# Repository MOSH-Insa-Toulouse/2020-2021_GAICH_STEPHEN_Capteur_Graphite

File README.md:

# 2020-2021 : Capteur Graphite GAICH-STEPHEN 
2020-2021 : Projet réalisé dans le cadre de l'Unité de Formation "du capteur au banc de test" en 4ème année Génie Physique, à l'INSA de Toulouse. Au cours de ce projet, nous avons réalisé un capteur de déformation/ jauge de contrainte à base de graphite 3H à 3B. Afin de mesurer la résistance de ce type de crayon, nous avons crée un dispositif bas-coût et transportable qui fut proposé par nos enseignants. Nous avons réalisé et fabriqué un PCB shield, à l'aide du logiciel Kicad, contenant un amplificateur transimpédance (circuit analogique) , un module Bluetooth, un écran OLED et un encodeur rotatoire. Ce dernier est pluggé sur un microcontrôleur Arduino Uno programmé à l'aide du logiciel Arduino IDE et contrôlé par une application android APK bluetooth. 

*** 
  - [Livrables](#livrables)
  - [PCB Shield](#pcb-shield)
  - [Code Arduino Mesure](#code-arduino-mesure)
  - [Application android APK](#application-android-apk)
  - [Banc de test](#banc-de-test)
  - [Code Arduino du banc de test](#code-arduino-du-banc-de-test)
  - [Protocole de test du capteur et les résultats obtenus](#protocole-de-test-du-capteur-et-les-résultats-obtenus)
  - [Datasheet capteur graphite](#datasheet-capteur-graphite)
  - [Problèmes rencontrés et améliorations à réaliser](#problèmes-rencontrés-et-améliorations-à-réaliser) 

*** 
## Livrables  

- [x] PCB shield 
- [x] Code Arduino permettant la mesure de R et le contrôle des fonctionnalités BT, OLED... 
- [x] Application android APK réalisé avec MIT APP INVENTOR.
- [x] Protocole de mesure et le programme Arduino pour le banc de test
- [x] Datasheet du capteur de déformation/ jauge de contrainte 

## PCB Shield
Utilisation des outils présents dans le logiciel Kicad pour créer le PCB: 
[KiCad EDA - Schematic Capture & PCB Design Software](https://kicad-pcb.org/), version: 5.1.8 

Le PCB Shield est pluggé sur un microcontrôleur Arduino Uno. Un amplificateur transimpédance, un module BT, un écran OLED et un encodeur rotatoire sont présents. 

Librairies de composants:
* Capacitor THT
* Resistor THT 
* Arduino Uno

#### Composants créés : symboles & empreintes 

- *Capteur Graphique*

- *Module Bluetooth*

- *Encodeur rotatoire Keyes KY 040*

- *Ecran OLED*

- *Amplificateur LT1050* (Empreinte déjà présente : DIP-8_W7.62mm_LongPads)

#### Schématique 

Dans le Eeschema, crée à partir d'un modèle Arduino Uno, nous avons regroupé les éléments suivant trois groupes : l'amplificateur transimpédance (circuit analogique qui permet de traiter les données envoyées par le capteur (variation de résistance)), les modules permettant d'ajouter des fonctionnalités au micro-contrôleur (module Bluetooth, encodeur rotatoire, écran OLED) et les broches de la carte Arduino Uno.  

#### Placement des composants 

#### Routage 3D

#### Soudage du PCB

Grâce à Catherine Crouzet, travaillant au Génie Physique, INSA Toulouse, nous avons pu réaliser notre PCB. Après avoir réalisé le schéma électrique, le placement des composants et le routage de la carte PCB sur le logiciel KiCad, le typon du PCB est imprimé sur deux feuilles calques. Les deux transparents sont alors superposés et scotchés entre eux afin de diminuer le risque de microcoupure (encre trop pale). Le typon est disposé sur la glace de l’insoleuse ainsi que la plaque d’époxy dont la face cuivrée (60µm) photosensible est "collée" au typon. Cette opération dure environ deux minutes et permet d’insoler la face photosensible. Le dessin du typon est alors visible sur la face cuivrée. La plaque est ensuite plongée dans un révélateur jusqu’à ce que le dessin apparaisse parfaitement (retire la résine non insolée). Après l’avoir rincé à l’eau, la plaque est alors prête pour la gravure. Le PCB est alors place dans un bain de perchlorure de fer rongeant tout le cuivre non protégé par la résine pendant sept minutes. Après l’avoir rincée à l’eau et vérifié le circuit, la résine est retirée avec de l’acétone. Le PCB sera ensuite percé et les composants seront soudés. 

Passons ensuite au perçage des trous de la plaquette à l'aide d'une perçeuse électrique [ici](Images/Perçeuse.jpg).
- 0.8mm pour ceux de l'AOP, des résistances et des capacités.
- 1mm pour ceux des connecteurs de l'Arduino et des headers des différents modules (pinces pour la feuille de graphite, bluetooth, encodeur rotatoire, écran OLED)

Pour finir, nous avons soudé chaque composant à l'aide d'un fer à souder. 

Remarque: il aurait fallu faire le diamètre des pads des connecteurs arduino plus gros afin d'avoir des soudures parfaites => peu de cuivre qui est resté autour après le perçage, ce qui a compliqué la soudure. 

#### Détail sur le conditionneur du capteur réalisé sur le shield (électronique analogique)
Nous avons détaillé cette partie dans la datasheet à la page 5 et 6 [ici](Datasheet/Datasheet_jauge_contrainte_GPINSA2021-2494-5215.pdf)

## Code Arduino Mesure 
Utilisation de l'environnement Arduino IDE téléchargeable [ici](https://www.arduino.cc/en/software); version 1.8.13.

Les librairies que nous avons utilisées sont disponibles [ici](PGM_Arduino_Mesure/Librairie).

Nous avons développé un programme permettant de mesurer la résistance de notre capteur. Vous pouvez le retrouver [ici](PGM_Arduino_Mesure/Programme_Capteur_Mesure/Programme_Capteur_Mesure.ino). 
Il s'agit d'un programme basique qui lira la valeur de la tension sur le pin A0 nommé comme "capteurgraphite". Cette acquisition est cadencée à 1s. La valeur lue est ensuite mappée sur 1 byte (0 à 255) car nous avons choisi d'envoyer un chiffre d'un byte sur le bluetooth. L'APK recevra un chiffre d'un byte à chaque tour de boucle. Cette valeur est également affichée sur le port série.

## Application android APK
Utilisation du site MIT App Inventor : [ici](https://appinventor.mit.edu/). 

Nous récupérons les données envoyées par le module bluetooth HC05 sur l'application et créons un fichier pour stocker ces dernières. 
Après de nombreux problèmes avec cet environnement et en s'inspirant du code crée par M.Grisolia, nous avons pu développer cette application. 

Face avant 

Une connexion avec le bluetooth HC05 est nécessaire. Puis, vous pourrez suivre la variation de la tension lue par l'APK "en direct". La valeur de la résistance du capteur est aussi calculée et affichée en bas de l'écran. Enfin, un fichier contenant toutes les données récupérées par le bluetooth est créé dans vos documents. 

Vous trouverez le fichier .aia [ici](APK_Bluetooth/CAPTEUR_GRAPHITE_FILE.aia) et le fichier .apk [ici](APK_Bluetooth/CAPTEUR_GRAPHITE_FILE.apk)

Nous avons essayé d'améliorer cette version en faisant plusieurs screens. 
Une page d'accueil présente ci-dessous : 

Ensuite, sur la deuxième page après avoir cliqué sur le bouton "commencer l'acquisition", vous devez réaliser la mesure de la résistance initiale du capteur. Lorsque tous les voyants de l'étape 1 se mettent au vert, vous pouvez voir le tracé de la variation de la tension Vadc en fonction du temps au cours du temps. Les valeurs de la résistance du capteur et de la résistance relative sont aussi affichées.

Vous trouverez le fichier .aia [ici](APK_Bluetooth/Application_Capteur_amelioree.aia) et le fichier .apk [ici](APK_Bluetooth/Application_Capteur_amelioree.apk)

Plusieurs améliorations peuvent être réalisées. Nous les détaillerons dans la partie "Problèmes rencontrés et améliorations à réaliser".

## Banc de test 
Nous avons réalisé deux bancs de test "low-tech". Nous avons détaillé sa construction dans la datasheet afin que toute personne possédant notre capteur puisse retrouver les résultats que nous avons obtenus [ici](Datasheet/Datasheet_jauge_contrainte_GPINSA2021-2494-5215.pdf) à la page 7-8. De plus, étant réalisé à base de déchets ménagers, aucun matériel de haute technologie n'est nécessaire. 

Nous vous présentons nos deux bancs de test : 

Figure : Banc de test « low-tech » n°1_ récupération de déchets divers

Figure : Banc de test « low-tech » n°2 _ carton

Au début, afin de diminuer les faux contacts entre les deux pinces crocodiles, nous avions utilisé un rouleau de papier toilette que nous avions troué (voir la photo ci-dessous).
Nous n'avons pas gardé cette méthode pour les mesures en tension et compression car les cercles créés sur le banc n'était pas à la même hauteur (amélioration possible).

## Code Arduino du banc de test 
Nous avons développé ce programme arduino afin de déterminer les valeurs obtenues en utilisant notre banc de test : [ici](PGM_Banc_de_test/PGM_Banc_de_test.ino).

Pour ce faire, nous avons du améliorer une librairie nous permettant de faire le "debouncing" sur l'encodeur rotatoire [ici](PGM_Arduino_Mesure/Librairie/Encoder_Polling_V2).

Notre nouveau programme gère aussi l'encodeur rotatoire et l'écran OLED. Ayant plusieurs banc de tests, nous avons programmé un menu sur l'écran OLED permettant à l'utilisateur de choisir le type de banc de test souhaité. Le boutton poussoir de l'encodeur rotatoire permet de selectionner ce dernier. Une fois le type de banc de test choisi, le programme envoie le type de banc de test à l'APK sous forme de "string" (texte). Dans le fichier des données enregistré sur le téléphone portable, chaque acquisition commence par des informations sur l'acquisition (banc de test, clock, forme des données reçues etc). Une fois cette étape terminée, l'OLED affiche la question "le bluetooth est- il connecté ?". L'utilisateur doit confirmer que la connexion a été établie en appuyant sur "Oui". Ensuite, il affiche "Etes-vous prêts ?" . L'utilisateur appuie de nouveau sur "Oui" une fois prêt. L'acquisition commence. La valeur de la tension Vadc est affichée sur l'OLED et est envoyée à l'APK via le bluetooth. Quand l'utilisateur souhaite arrêter l'acquistion, il doit appuyer sur le bouton 'STOP'. L'acquisition est alors arrêtée et l'OLED affiche de nouveau le menu principal.

## Protocole de test du capteur et les résultats obtenus 
Nous avons réalisé différentes expériences afin de déterminer les caractéristiques de notre capteur. 

#### Influence des dimensions du capteur 

Dans un premier temps, nous avons souhaité étudier l'influence des dimensions du capteur sur la résistance initiale. De ce fait, nous avons réalisé un plan d'expérience avec un modèle linéaire sans interactions de type TRI. Veuillez consulter ce document pour plus de détails sur la démarche : [ici](Banc_de_test&résultats/Banc_test_recherche_meilleur_capteur.docx) et sur les résultats obtenus [ici](Banc_de_test&résultats/Plan d'expérience_meilleures_dimensions.xlsx).

Nous avons pu identifier la réalité expérimentale (variables aléatoires de mesure) et tenter d’expliquer puis de maitriser au mieux les paramètres ayant un impact sur la résistance de notre capteur. Nous n’assurons pas que tous les paramètres influents furent identifiés. Elles ont aussi permis de vérifier que la résistance de notre capteur suivait la loi de Pouillet et donc la loi d’Ohm. Etant donné que nous ne sommes pas capables de déterminer le nombre de feuillets de graphite déposé lors du coloriage de notre capteur, nous allons étudier la variation relative en résistance ∆R/R_o = (R_mes-R_o)/R_o  afin d’homogénéiser nos mesures et pouvoir les comparer.  

#### Zone de non-déterioration du capteur

Dans un deuxième temps, nous nous avons essayé de determiner la zone de non-destruction du capteur. Après chaque mesure sur un rayon de courbure, nous avons noté la valeur de la tension du capteur au repos (non déformé) puis avons déterminé la résistance de ce dernier. Nous l’avons ensuite comparé à celle mesurée au début de la série de mesure. 
Document excel  [ici](Banc_de_test&résultats/Determination_zone_non_destruction_capteur.xlsx)

Figure : |Vadc_après_chaque_mesure - Vadc_initiale| après chaque déformation pour le capteur en tension

Figure : |Vadc_après_chaque_mesure - Vadc_initiale| après chaque déformation pour le capteur en compression

Voici notre conclusion : 

#### Influence du type de crayon utilisé pour colorier le capteur

Ensuite, nous avons étudie l'influence du type de crayon utilisé pour colorier notre capteur. Les crayons 3H, 2H, H, HB, B, 2B, et 3B furent testés successivement pour colorier notre capteur. Des tests de déformation, utilisant différents rayons de courbure de notre banc de test, sur ces capteurs furent réalisés. Ces informations sont présentes sur ces différents graphiques. Pour de détails, consultez le document excel [ici](Banc_de_test&résultats/Mesure_RayonCoubure_Crayons_Papiers.xlsx). 

Figure : Graphique représentant la variation relative de la résistance en fonction de la déformation en tension du capteur et du type de crayon présent sur le capteur

Figure : Graphique représentant la variation relative de la résistance en fonction de la déformation en compression du capteur et du type de crayon présent sur le capteur

En conclusion de cette étude, le capteur colorié avec un crayon 3H est le plus sensible. En effet, pour ce capteur, la variation relative de la résistance ΔR/Ro est la plus grande. Cependant, en effectuant plusieurs expériences (colorier différents capteurs avec ce crayon), nous observons une large variabilité de la réponse. Lorsque le capteur est colorié avec des crayons 2H, H, HB, B, 2B et 3B, un comportement linéaire du ce dernier est observé. La sensibilité se définit comme le rapport entre sa valeur de sortie et sa valeur d'entrée. Lorsque le capteur est soumis à un mouvement de tension et de compression, la sensibilité du capteur augmente avec la dureté du crayon utilisé. En l’occurrence, le capteur colorié avec le crayon 3H est le plus sensible et celui colorié avec le crayon 3B est le moins sensible.

#### Influence du type de papier du capteur 

Enfin, nous avons étudié l'influence de type de papier. Nous avions émis l'hypothèse que la réponse du capteur serait différente en fonction du type de papier utilisé. Quand le capteur est réalisé sur du papier normal (70g/m²), la valeur de la résistance est trop faible pour être mesurée par notre conditionneur. La valeur de la tension Vadc est en saturation (5V). Une corrélation entre l’épaisseur du papier utilisé et la réponse du capteur existe. Nous avons détaillé une possible explication à ce phénomène dans la datasheet à la page 15. [ici](Datasheet/Datasheet_jauge_contrainte_GPINSA2021-2494-5215.pdf)

Pour pallier ce problème, le papier fut renforcé en enveloppant le capteur avec du ruban d’adhésif sans couvrir les pads du capteur pour la prise du contact avec les pinces crocodiles. Vous trouverez les résultats obtenus dans le fichier excel [ici](Banc_de_test&résultats/Influence_scotch.xlsx). En effectuant plusieurs tests sur le capteur, une tendance d'augmentation de la résistance est observée lorsque nous diminuons le rayon de courbure. Cependant, nous pouvons observer une augmentation initiale de la résistance entre un capteur scotché et un capteur sans ruban adhésif. Nous n’avons pas observé une amélioration de la zone de non-destruction. Dans certains cas, nous observons même une dégradation de cette dernière. Nous avons détaillé une possible explication à ce phénomène dans la datasheet à la page 15. [ici](Datasheet/Datasheet_jauge_contrainte_GPINSA2021-2494-5215.pdf)

## Datasheet capteur graphite
Vous pouvez retrouver la datasheet complète de notre capteur [ici](Datasheet/Datasheet_jauge_contrainte_GPINSA2021-2494-5215.pdf)

## Problèmes rencontrés et améliorations à réaliser

#### Problèmes sur le PCB

- Pads pour les connecteurs arduino trop fins.
- Mauvais placement de l'empreinte OLED : En testant l'écran OLED avec un programme fourni dans les libraires arduino, nous nous sommes rendus compte que, par inattention, nous avions mal placé l'empreinte (rotation 180°) car nous souhaitions que l'écran OLED soit positionné vers l'extérieur (cf PCB 3D). Afin d'avoir les bonnes pins, ce dernier doit être placé à l'intérieur. Or il y a l'encodeur rotatoire. Pour palier à ce problème, nous allons utiliser la platine d'expérimentation ou des fils males/femelle. 

  Améliorations : Nouveau PCB. 

#### Amélioration de l'application APK : Application capteur améliorée 
Après de multiples essais, nous n'avons pas réussi à afficher correctement la variation (dR-Ro)/Ro. Nous ne comprenons pas l'erreur commise. 
De plus, il faudrait optimiser le code pour que le traçage sur le canvas et les calculs de résistance se fassent en "temps réel". Nous avons un temps de décalage assez important. 
  
#### Améliorations sur la caractérisation du capteur 

Veuillez vous référer à notre datasheet présente [ici](Datasheet/Datasheet_jauge_contrainte_GPINSA2021-2494-5215.pdf) section Suggestions/Remarques. 

Nous avons détaillé différentes expérimentations que nous aurions aimées mener. Par manque de temps, nous n'avons pu les faire. 
De plus, afin de determiner concrètement les dimentions optimales du capteur, le plan d'expérience que nous avons mené devrait être complété par une étude plus approfondie (modèle de 2nd ordre) pour determiner l'optimum. Cependant, il faut pouvoir maitriser des paramètres qui ne sont pas contrôlables pour le moment (nombre de feuillets de graphite sur le capteur). 

***

## Note des auteurs 
Nous tenons à remercier Mme Crouzet, M.Grisolia et M.Biganzoli pour leur aide tout au long de ce projet ainsi que M.Constancias pour son aide lors de l'analyse des résultats obtenus sur notre DOE. 

Pour nous contacter : 
- Eléonore Gaich : gaich@etud.insa-toulouse.fr
- Calvin Stephen : stephen@etud.insa-toulouse.fr

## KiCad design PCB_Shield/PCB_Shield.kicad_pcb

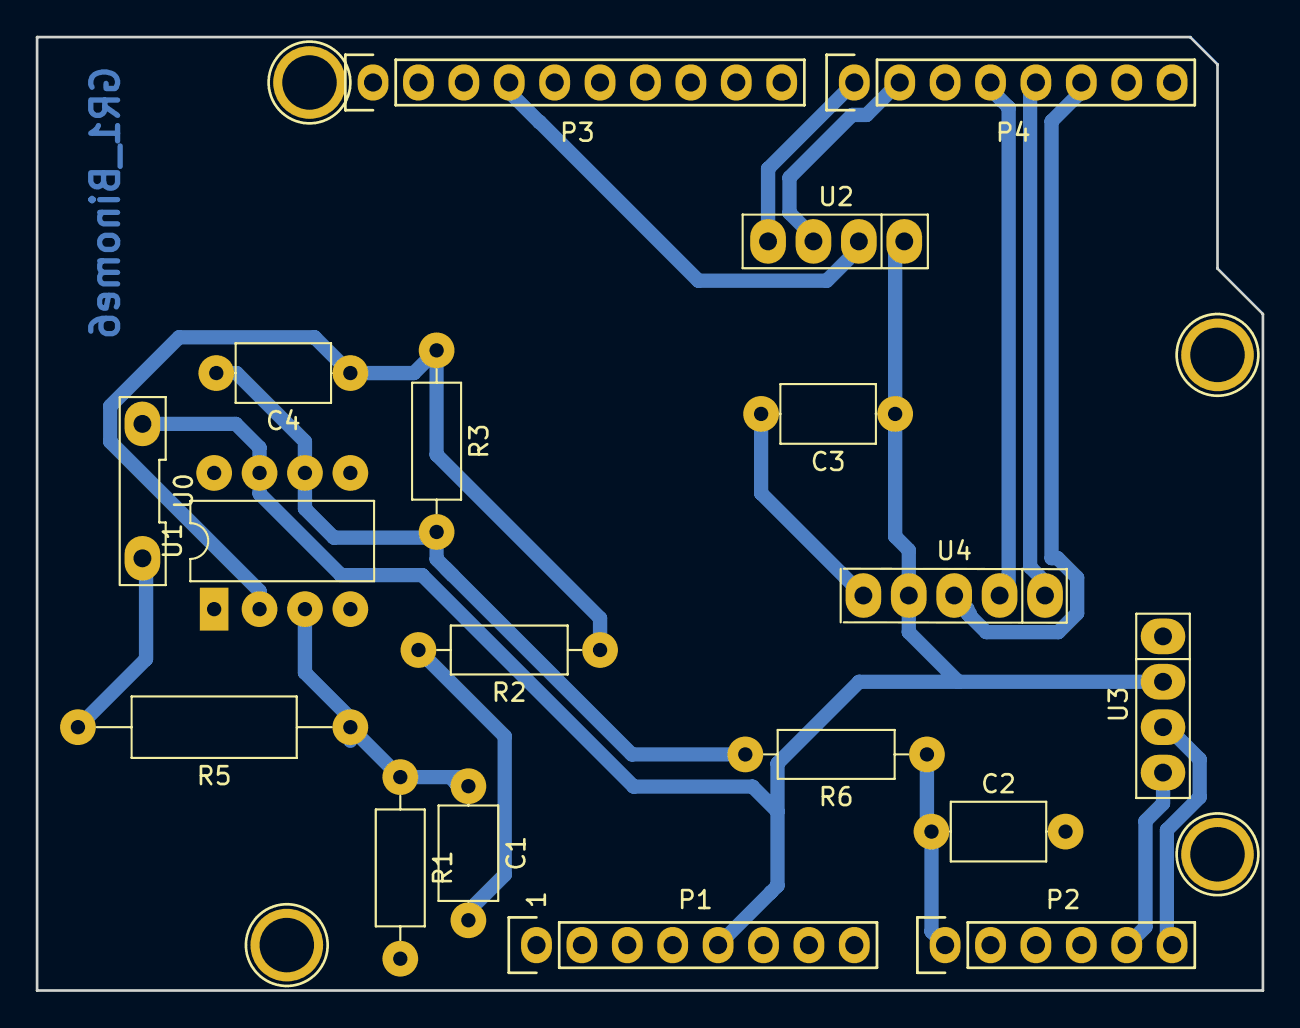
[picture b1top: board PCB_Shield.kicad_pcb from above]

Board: 2 copper layers, 68.6 x 53.3 mm, 22 parts (0 on the bottom side), 14 nets.

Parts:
C1, C2, C3: 100n; C_Axial_L5.1mm_D3.1mm_P7.50mm_Horizontal
C4: 1µ; C_Axial_L5.1mm_D3.1mm_P7.50mm_Horizontal
P1: Power; Socket_Strip_Arduino_1x08
P2: Analog; Socket_Strip_Arduino_1x06
P3: Digital; Socket_Strip_Arduino_1x10
P4: Digital; Socket_Strip_Arduino_1x08
P5, P6, P7, P8: CONN_01X01; Arduino_1pin
R1, R3: 100k; R_Axial_DIN0207_L6.3mm_D2.5mm_P10.16mm_Horizontal
R2, R6: 1k; R_Axial_DIN0207_L6.3mm_D2.5mm_P10.16mm_Horizontal
R5: 10k; R_Axial_DIN0309_L9.0mm_D3.2mm_P15.24mm_Horizontal
U0: CG
U1: LTC1050; DIP-8_W7.62mm_LongPads
U2: BT_HC-05; Bluetooth_HC-05
U3: Ecran_OLED
U4: Rot_Keyes_KY-040; Rot_Keyes_ky-040

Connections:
+5V: C3.1, P1.5, U0.1, U1.7, U2.2, U3.2, U4.4
ADC: C2.1, P2.1, R6.1
CLK: P4.5, U4.1
DATA: P4.4, U4.2
GND: C1.2, C2.2, C3.2, P1.6, P1.7, P3.4, R1.2, R2.2, U1.4, U2.3, U3.1, U4.5
unnamed: C1.1, R1.1, R5.1, U1.3
unnamed: C4.1, R2.1, R3.1, U1.2
unnamed: C4.2, R3.2, R6.2, U1.6
unnamed: R5.2, U0.2
Rx: P4.1, U2.5
SCL: P2.6, P3.1, U3.3
SDA: P2.5, P3.2, U3.4
SWITCH: P4.6, U4.3
Tx: P4.2, U2.4

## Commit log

2021-03-03 Create Kicad_PCB
2021-03-03 Ajout de la partie PCB Shield au projet Capteur_Graphite.
2021-03-03 Ajout différents répertoires
2021-03-08 Modification PCB _ test routage
2021-03-09 Images_Readme
2021-03-09 Actualisation lib capteur
2021-03-09 Ajout image
2021-03-09 Ajout_images
2021-03-09 Ajout_new_images
2021-03-09 Ajout_Images_new
2021-03-09 New_images
2021-03-09 Modif_PCB_Nom
2021-03-09 Images
2021-03-10 Images_New
2021-03-10 Modification_TD
2021-03-10 Modif_TD
2021-03-10 Delete
2021-03-10 Ajout
2021-03-10 Modif_10-03-2021
2021-03-11 Modif 11-03
2021-03-17 Modif_17-03
2021-03-17 Modif 17-03
2021-03-18 Erreur_bluetooth_ok
2021-03-18 Modif 18-03
2021-03-24 programme version plus recente
2021-03-24 Test
2021-04-08 Modif 08-04
2021-04-08 modification
2021-04-08 Modif 8-04
2021-04-10 Banc de test news
2021-04-10 News Datasheet
2021-04-11 A faire
2021-04-11 Modif 11-04
2021-04-12 Modif 12-4
2021-04-13 Menu OLED
2021-04-13 OLED MENU
2021-04-13 Modif 13-04
2021-04-13 Modelisation capteur
2021-04-13 Modif 13-4 21h20
2021-04-14 OLED Affigage tension
2021-04-14 Banc_de_test_OLED
2021-04-14 Test_module
2021-04-14 Libraries et modification programme Banc_de_test
2021-04-14 Librairies
2021-04-16 Banc de test mise à jour
2021-04-16 Modif matrice hadamard
2021-04-19 Banc de test
2021-04-19 Mesures
2021-04-21 Banc de test_DOE
2021-04-21 A faire readme
2021-04-22 Banc de test session 22-04
2021-04-26 Modif Banc de test
2021-04-26 Modif Datasheet Description du Fonctionnement du capteur
2021-04-26 Modifier 26-04
2021-04-27 Commentaires Mesures
2021-04-28 Modif Courbes
2021-04-28 Datasheet
2021-04-28 Suppression a faire
2021-04-28 Modif_datasheet
2021-04-29 Datasheet 29-04 18h
2021-05-01 Completer datasheet
2021-05-01 A faire supp
2021-05-01 Banc_test_resultats
2021-05-01 Photo
2021-05-01 Banc_de_test
2021-05-01 Datasheet+images
2021-05-01 Changement_nom_github
2021-05-01 apkfile
2021-05-01 Modif graphes zone de non destruction et mis à jour du code banc de test
2021-05-01 Modif program banc de test
2021-05-01 Mis en forme et commentaire pour le code banc de test et PGM Captuer Mesure
2021-05-02 Figures determination zone de non destruction
2021-05-03 Excel Determination_zone_non_destruction_capteur
2021-05-03 APK + soutenance
2021-05-05 APK_Banc_de_test_derniere_modif
2021-05-05 Suppression pour avoir commentaire "commit" de FIN DE PROJET
2021-05-05 FIN DE PROJET
